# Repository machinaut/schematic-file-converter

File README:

A command line python anything-in anything-out file converter to go between the multitude of electrical circuit schematic file formats. This project was started by Alex Ray (ajray@ncsu.edu), on behalf of Upverter (http://upverter.com).

How to use:
```bash
./converter.py -i test.sch -f kicad -t json -o test.json

-i: input file
-f: from format
-t: to format
-o: output file
```

Where to Get Help:
```bash
./converter.py -h
```

Supported Formats:
  The converter started with support for KiCad. We have since been expanding it to support many of the popular open and closed source formats, as follows.
* KiCad
* Eagle (in development)
* gEDA (in development)
* Fritzing (in development)
* Altium (in development)

Format Wish List:
  This is the list of formats we wish we supported, and will work on someday (hopefully soon!). We are looking for developers to help us so please ping us if you're interested!
* DXDesigner & PADs
* Alegro
* OrCad

The Concept:
  To use an Upverter Open JSON export in another piece of software, you will need to convert it into that software's proprietary format. Likewise, to get your data out of another piece of software and import it into Upverter, you will also need to run their export through the converter. We are working to make this easier, but we will largely depend on community contribution and the participation of the other vendors.

Interchange Format Documentation:
  The converter is based on the Upverter Open JSON Format fully documented at http://upverter.com/resources/open-json-format/. We hope that someday all of the major providers of schematic capture software will support interoperability with open formats like this one.

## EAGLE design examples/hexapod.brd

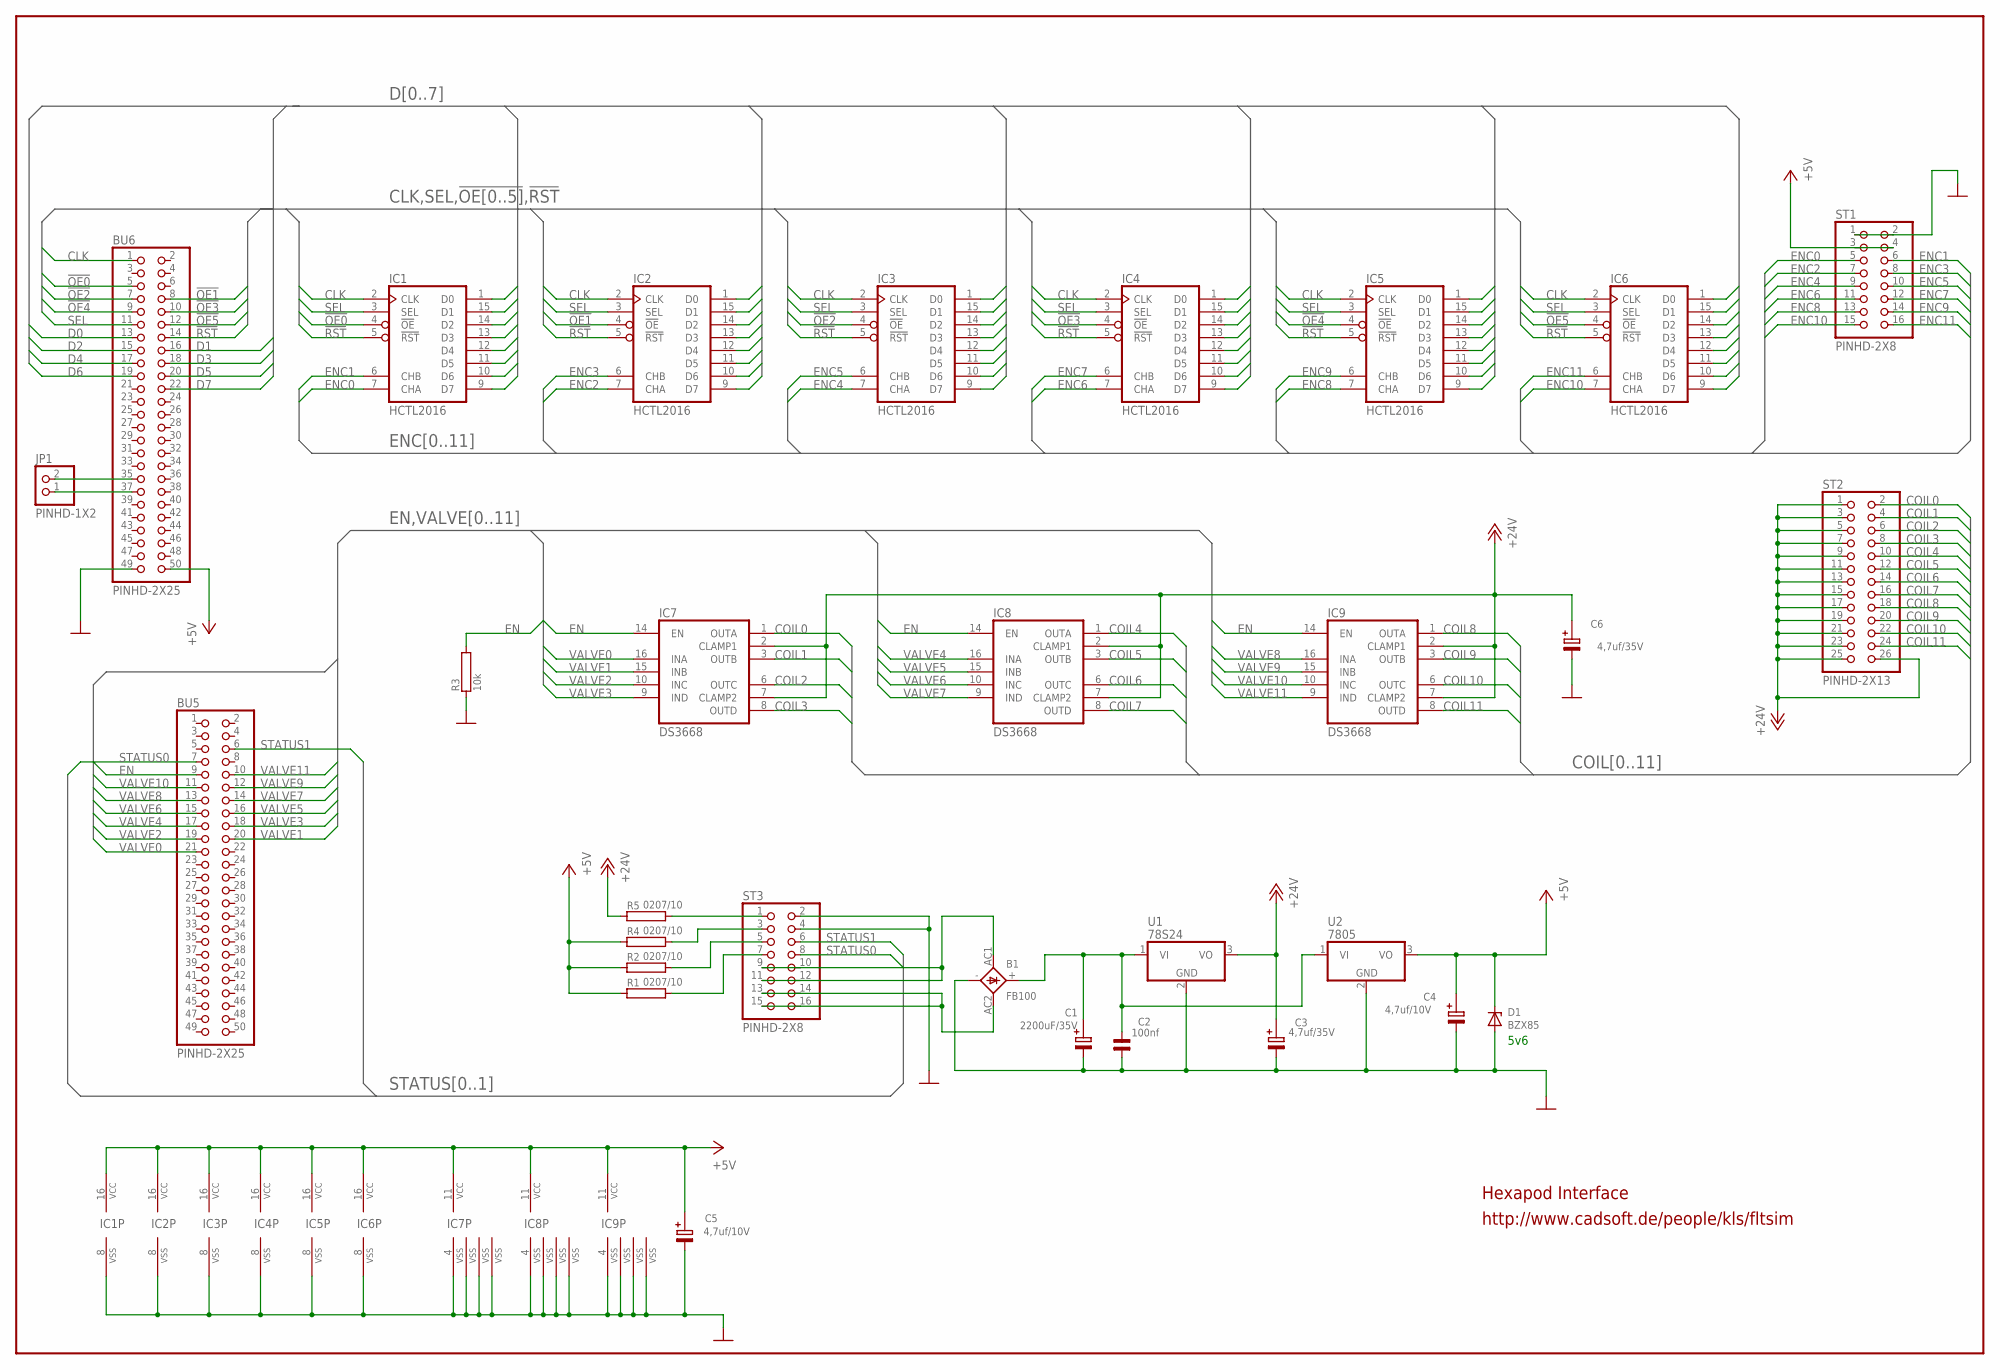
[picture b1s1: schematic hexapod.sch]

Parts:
B1: FB100
BU5, BU6: PINHD-2X25; 2X25
C1: 2200uF/35V; E35-16
C2: 100nf; C5B2,5A
C3, C6: 4,7uf/35V; E2,5-5
C4, C5: 4,7uf/10V; E2,5-5
D1: BZX85; DO41Z10
IC1, IC2, IC3, IC4, IC5, IC6: HCTL2016; DIL-16
IC7, IC8, IC9: DS3668; DIL-16
JP1: PINHD-1X2; 1X02
R1, R2, R4, R5: 0207/10
R3: 10k; 0207/10@1
ST1, ST3: PINHD-2X8; ML16
ST2: PINHD-2X13; ML26
U1: 78S24; TO220H
U2: 7805; TO220H

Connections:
!OE0: BU6.5, IC1.4 (!OE)
!OE1: BU6.8, IC2.4 (!OE)
!OE2: BU6.7, IC3.4 (!OE)
!OE3: BU6.10, IC4.4 (!OE)
!OE4: BU6.9, IC5.4 (!OE)
!OE5: BU6.12, IC6.4 (!OE)
!RST: BU6.14, IC1.5 (!RST), IC2.5 (!RST), IC3.5 (!RST), IC4.5 (!RST), IC5.5 (!RST), IC6.5 (!RST)
+5V: BU6.50, C4.+, C5.+, D1.K, IC1.16 (VCC), IC2.16 (VCC), IC3.16 (VCC), IC4.16 (VCC), IC5.16 (VCC), IC6.16 (VCC), IC7.11 (VCC), IC8.11 (VCC), IC9.11 (VCC), R1.1, R2.1, R4.1, ST1.3, ST1.4, U2.3 (VO)
+24V: C3.+, C6.+, IC7.2 (CLAMP1), IC7.7 (CLAMP2), IC8.2 (CLAMP1), IC8.7 (CLAMP2), IC9.2 (CLAMP1), IC9.7 (CLAMP2), R5.1, ST2.1, ST2.3, ST2.5, ST2.7, ST2.9, ST2.11, ST2.13, ST2.15, ST2.17, ST2.19, ST2.21, ST2.23, ST2.25, ST2.26, U1.3 (VO)
AC1: B1.AC1, ST3.9, ST3.10, ST3.11, ST3.12
AC2: B1.AC2, ST3.13, ST3.14, ST3.15, ST3.16
CLK: BU6.1, IC1.2 (CLK), IC2.2 (CLK), IC3.2 (CLK), IC4.2 (CLK), IC5.2 (CLK), IC6.2 (CLK)
COIL0: IC7.1 (OUTA), ST2.2
COIL1: IC7.3 (OUTB), ST2.4
COIL2: IC7.6 (OUTC), ST2.6
COIL3: IC7.8 (OUTD), ST2.8
COIL4: IC8.1 (OUTA), ST2.10
COIL5: IC8.3 (OUTB), ST2.12
COIL6: IC8.6 (OUTC), ST2.14
COIL7: IC8.8 (OUTD), ST2.16
COIL8: IC9.1 (OUTA), ST2.18
COIL9: IC9.3 (OUTB), ST2.20
COIL10: IC9.6 (OUTC), ST2.22
COIL11: IC9.8 (OUTD), ST2.24
D0: BU6.13, IC1.1 (D0), IC2.1 (D0), IC3.1 (D0), IC4.1 (D0), IC5.1 (D0), IC6.1 (D0)
D1: BU6.16, IC1.15 (D1), IC2.15 (D1), IC3.15 (D1), IC4.15 (D1), IC5.15 (D1), IC6.15 (D1)
D2: BU6.15, IC1.14 (D2), IC2.14 (D2), IC3.14 (D2), IC4.14 (D2), IC5.14 (D2), IC6.14 (D2)
D3: BU6.18, IC1.13 (D3), IC2.13 (D3), IC3.13 (D3), IC4.13 (D3), IC5.13 (D3), IC6.13 (D3)
D4: BU6.17, IC1.12 (D4), IC2.12 (D4), IC3.12 (D4), IC4.12 (D4), IC5.12 (D4), IC6.12 (D4)
D5: BU6.20, IC1.11 (D5), IC2.11 (D5), IC3.11 (D5), IC4.11 (D5), IC5.11 (D5), IC6.11 (D5)
D6: BU6.19, IC1.10 (D6), IC2.10 (D6), IC3.10 (D6), IC4.10 (D6), IC5.10 (D6), IC6.10 (D6)
D7: BU6.22, IC1.9 (D7), IC2.9 (D7), IC3.9 (D7), IC4.9 (D7), IC5.9 (D7), IC6.9 (D7)
EN: BU5.9, IC7.14 (EN), IC8.14 (EN), IC9.14 (EN), R3.2
ENC0: IC1.7 (CHA), ST1.5
ENC1: IC1.6 (CHB), ST1.6
ENC2: IC2.7 (CHA), ST1.7
ENC3: IC2.6 (CHB), ST1.8
ENC4: IC3.7 (CHA), ST1.9
ENC5: IC3.6 (CHB), ST1.10
ENC6: IC4.7 (CHA), ST1.11
ENC7: IC4.6 (CHB), ST1.12
ENC8: IC5.7 (CHA), ST1.13
ENC9: IC5.6 (CHB), ST1.14
ENC10: IC6.7 (CHA), ST1.15
ENC11: IC6.6 (CHB), ST1.16
GND: B1.-, BU6.49, C1.-, C2.1, C3.-, C4.-, C5.-, C6.-, D1.A, IC1.8 (VSS), IC2.8 (VSS), IC3.8 (VSS), IC4.8 (VSS), IC5.8 (VSS), IC6.8 (VSS), IC7.4 (VSS), IC7.5 (VSS), IC7.12 (VSS), IC7.13 (VSS), IC8.4 (VSS), IC8.5 (VSS), IC8.12 (VSS), IC8.13 (VSS), IC9.4 (VSS), IC9.5 (VSS), IC9.12 (VSS), IC9.13 (VSS), R3.1, ST1.1, ST1.2, ST3.2, ST3.4, U1.2 (GND), U2.2 (GND)
unnamed: R5.2, ST3.1
unnamed: R4.2, ST3.3
unnamed: R2.2, ST3.5
unnamed: R1.2, ST3.7
unnamed: BU6.35, JP1.2
unnamed: BU6.37, JP1.1
SEL: BU6.11, IC1.3 (SEL), IC2.3 (SEL), IC3.3 (SEL), IC4.3 (SEL), IC5.3 (SEL), IC6.3 (SEL)
STATUS0: BU5.7, ST3.8
STATUS1: BU5.6, ST3.6
VALVE0: BU5.21, IC7.16 (INA)
VALVE1: BU5.20, IC7.15 (INB)
VALVE2: BU5.19, IC7.10 (INC)
VALVE3: BU5.18, IC7.9 (IND)
VALVE4: BU5.17, IC8.16 (INA)
VALVE5: BU5.16, IC8.15 (INB)
VALVE6: BU5.15, IC8.10 (INC)
VALVE7: BU5.14, IC8.9 (IND)
VALVE8: BU5.13, IC9.16 (INA)
VALVE9: BU5.12, IC9.15 (INB)
VALVE10: BU5.11, IC9.10 (INC)
VALVE11: BU5.10, IC9.9 (IND)
VIN: B1.+, C1.+, C2.2, U1.1 (VI), U2.1 (VI)

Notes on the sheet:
Hexapod Interface
5v6
http://www.cadsoft.de/people/kls/fltsim

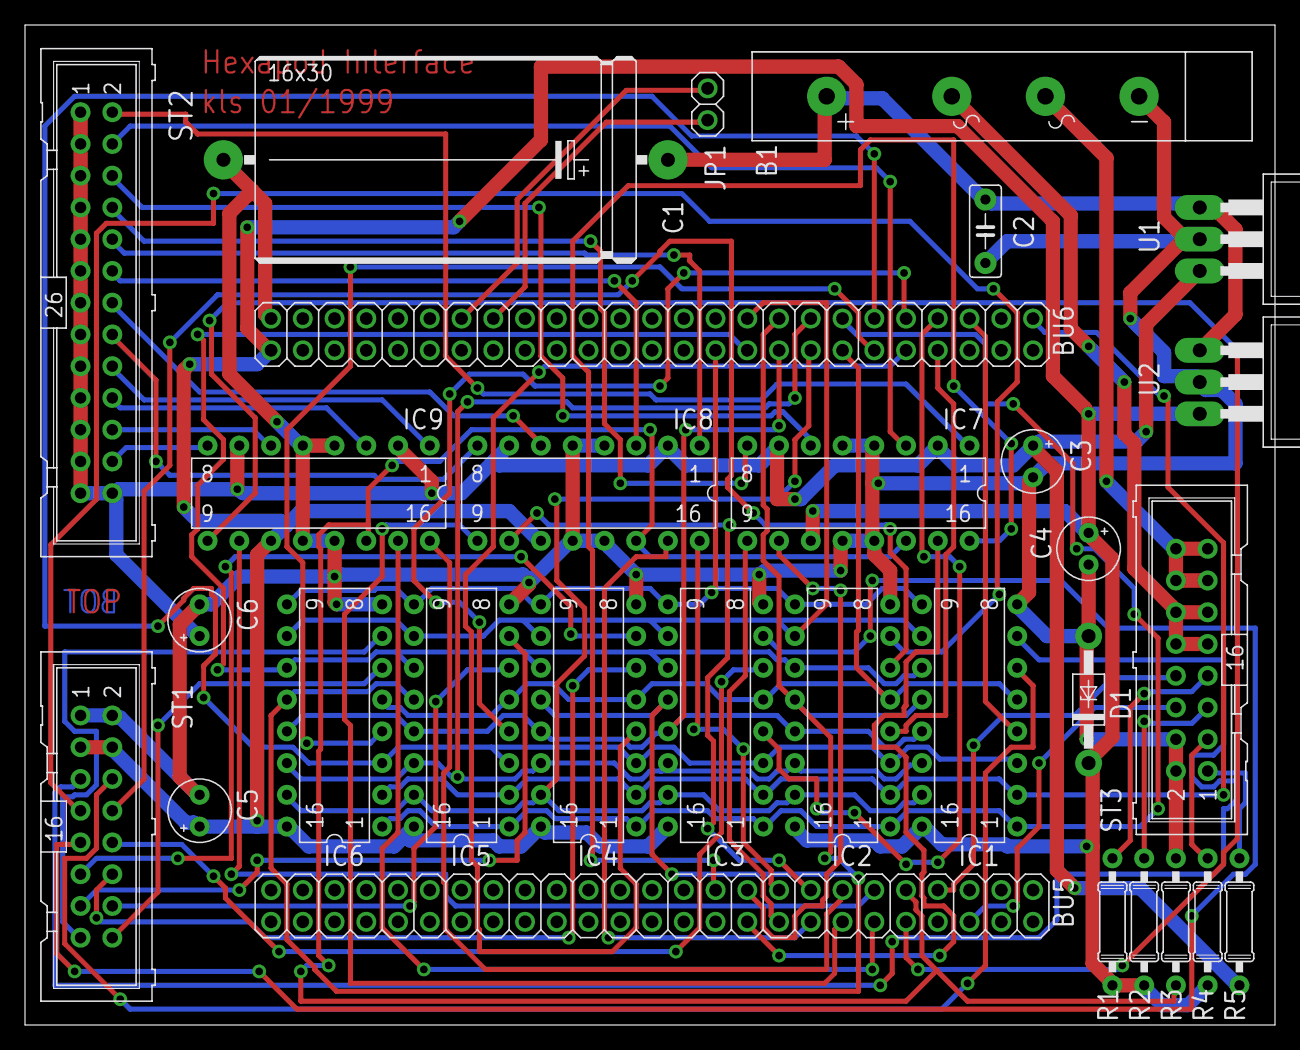
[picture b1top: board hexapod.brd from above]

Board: 2 copper layers, 100.0 x 80.0 mm, 30 parts (0 on the bottom side), 68 nets.

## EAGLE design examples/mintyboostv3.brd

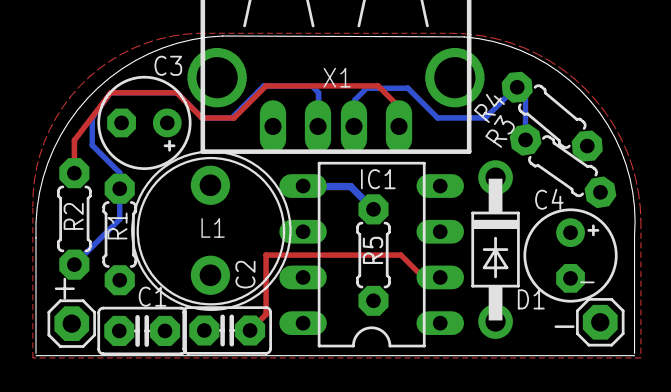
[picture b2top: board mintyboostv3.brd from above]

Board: 2 copper layers, 33.3 x 17.8 mm, 15 parts (0 on the bottom side), 8 nets.

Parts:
+: 1X01
-: 1X01
C1, C2: 0.1uF; C025-025X050
C3, C4: 220uF; E2,5-5
D1: 1N5817; DO41-7
IC1: LT1302; DIL08
L1: L; 6000
R1, R3: 49.9K; 0204/5
R2, R4: 75K; 0204/5
R5: 3.3k; 0204/5
X1: PN87520

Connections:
+5V: C4.+, D1.C, IC1.4, R2.1, R4.1, X1.1
BATT+: +.1, C1.1, C3.+, IC1.6, L1.1
D+: R1.2, R2.2, X1.3
D-: R3.2, R4.2, X1.2
GND: -.1, C1.2, C2.2, C3.-, C4.-, IC1.1, IC1.3, IC1.8, R1.1, R3.1, R5.1, X1.4
unnamed: C2.1, IC1.2
unnamed: IC1.5, R5.2
unnamed: D1.A, IC1.7, L1.2

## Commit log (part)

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2011-10-06 initial commit, beginning parsing kicad files
2011-10-06 json file format doc
2011-10-06 some classes, and trying to be smarter (dumber) about kicad format
2011-10-07 heading in for the night
2011-10-07 makin it smaller
2011-10-07 now making it more classy
2011-10-07 got segments dividing up correctly, now to clean up the debugging stuff
2011-10-07 fuck yeah, connection works
2011-10-07 woot sane net creation works
2011-10-07 removed old net calculation functions
2011-10-07 now prettyprints JSON for the nets
2011-10-07 now outputs full json, but only nets are populated
2011-10-07 rename connpoints to junctions
2011-10-08 ignore swp files
2011-10-08 remove swap files
2011-10-09 components almost there
2011-10-13 added the command to run the scritp to the README file
2011-10-13 more thinking on the format, gonna play with rendering jsonformat.json
2011-10-13 rename file
2011-10-17 nothing to see here
2011-10-19 render python script now generates basic component instances, and fully renders the example file (as it is now)
2011-10-21 removed old file format spec and added an example json file
2011-10-21 updated the example json file
2011-10-29 updating the readme file.
2011-10-29 reorg of the files.
2011-10-29 cleanup.
2011-10-29 more cleanup...
2011-10-29 polishing the documentation.
2011-10-29 last of the first pass cleanup.
2011-11-04 python script to generate an Eagle User-Level-Program that will output JSON
2011-11-04 ulp script that exporter is supposed to look like
2011-11-04 eagle type system representation in JSON. I love the meta
2011-11-04 minor todo added
2011-11-04 now ironically using an eagle representation itself in JSON
2011-11-04 Adding a file for stuff i am working on, to keep from borking the main files
2011-11-04 changing the printery things to just go to stdout for now
2011-11-04 place where one-off scripts go to die
2011-11-04 eagle barfer is tentatively done
2011-11-04 Adding template files for uvp package, which will be classes that handle uvp files
2011-11-04 Adding example upverter file json formapt
2011-11-04 json ulp changes, less whitespace
2011-11-04 typo in eagle.json, propagated
2011-11-04 Adding my orderer... I'll finish this tonight.
2011-11-05 Pushing before zzzzzz.....
2011-11-05 One useless file in up in hurrr.
2011-11-05 im about to pass out
2011-11-05 going into a programming competition, theyre going to take my laptop, see yall on the other side
2011-11-06 I made a little progress on the net class for the .uvp json format library.
2011-11-06 PREPARRE TO MERGE
2011-11-06 clean up random shit into ajray
2011-11-06 I DO ORDAIN A NEW SCHEMATIC HEIRARCHY
2011-11-06 Eagle XML format has arrived
2011-11-06 Added that the parser grabs the xml of the eagle file.
2011-11-06 Fixed previous commit
2011-11-06 Continuing to work on the xml, the xml is now in.
2011-11-06 I have a new basic strategy for eagle....
2011-11-06 multiple things
2011-11-06 make actual inclusion work and sanely print help message when run incorrectly
2011-11-06 Adding michael's schematic in the new eagle xml format, so we can nom nom nom the file into the upverter json format.
2011-11-06 eaglexml file input type
2011-11-06 eaglexml.py file, forgot last time
2011-11-06 More stuff...
2011-11-06 Getting rid of my crap.
2011-11-06 more normal-y eaglexml
2011-11-06 working on marshalling
2011-11-06 working on xml input parser
2011-11-06 makin dem shapes.
2011-11-06 Commit before fallin' asleep.
2011-11-06 rest of example file is accounted for, still does nothing on eagle xml input parsing side
2011-11-06 Cleaned up the shape.py a little bit. I need to look through the xml files, and see how shapes are defined, and create alternate constructors ( that is what the @classmethod stuff is all about) that 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
2011-11-06 gEDA/gaf File Format Document started
2011-11-06 Coordinate Space added
2011-11-06 Filenames added
2011-11-06 Object types added
2011-11-06 gEDA specific TODO file added
2011-11-06 version element added
2011-11-06 line element added
2011-11-06 layout cleanup
2011-11-06 Playing with print statements, so I understand just what we are getting from the xml. No substantial changes.
2011-11-06 picture element added
2011-11-06 Revert "Playing with print statements, so I understand just what we are getting from the xml. No substantial changes."
    This reverts commit bca2fc1c63188a0ede8de8b3fdd6b3c210425f12.
2011-11-06 box element added
2011-11-06 circle element added
2011-11-06 layout cleanup: code -> pre
2011-11-06 layout cleanup: breaks
2011-11-06 minor layout cleanups
2011-11-06 arc element added
2011-11-06 more cleaning, testing on the interpreter, seems that everything works.
2011-11-06 text element added
2011-11-06 net element added
2011-11-06 table tag closed
2011-11-06 Too much Java rots the brain.
2011-11-06 bus element added
2011-11-06 pin element added
2011-11-06 layout cleanup ... m(
2011-11-06 More progress on component.py
2011-11-06 path element added
2011-11-06 character element added
2011-11-06 Colors section added
2011-11-06 Attributes section added
2011-11-06 Embedded Components section added
2011-11-06 minor emphasis
2011-11-06 Path data section added
2011-11-06 document revision section added
2011-11-06 minor typo corrected
2011-11-06 more verbosity in eaglexml libraries
2011-11-06 Push before meetup at garage. Also, Alex, popese. That is all.
2011-11-06 more xml junk
2011-11-06 Fixed syntax
2011-11-06 More changes
2011-11-06 newpin function for shortness
2011-11-06 core/component.py is now mostly sane and has been test
2011-11-07 Added component instance beginnings
2011-11-07 instance.py
2011-11-07 more classy-ness for the core libs
2011-11-07 woot parses an instance now, just badly
2011-11-07 splitting
2011-11-07 instance parsing in eaglexml
2011-11-07 Working on eaglexml of parsing libraries, trying to get the libraries to give us something coherent for our pretty classes
2011-11-07 added the library id for library components
2011-11-07 started submitting, but still fails
2011-11-07 calling it a night, still needs to fix the component neess
2011-11-07 working on cleaning up the classes structures, in preparation for creating a recursing
2011-11-07 waaay simpler example
2011-11-07 added bogus design_attributes to put something in there
2011-11-07 removing useless shit
2011-11-07 removing test file
2011-11-07 still cleaning eaglexml.py
2011-11-07 fixed the cap example
2011-11-07 trying to fix core/design.py
2011-11-07 Forgot to add these files last time. Cleaning up core, making it more well rounded, and trying to fix stuff.
2011-11-07 cleaning up namespace, throughly checked the types of file version, component instance, design attribute, annotation, and attribute, however, i need to check the rest.
2011-11-07 parser/eaglexml.py is now got functions!
2011-11-07 prettify all of the things
2011-11-07 parser/eaglexml.py is now mostly recursive descent
2011-11-07 parser/eaglexml.py reordering parsing in order of descent
2011-11-07 fix readme usage statement
2011-11-07 add examples to readme
2011-11-07 rename json parser to openjson to let us use import json in it
2011-11-07 working on the openjson parson now
2011-11-07 parser/openjson.py open for business, minus nets
2011-11-07 parser/openjson.net appears to support nets as well. bring on the conversions
2011-11-07 bringing the eaglexml back into spec
2011-11-07 woo! think i fixed openjson parsing -> outputting
2011-11-07 header comments
2011-11-07 tiny UPV example
2011-11-07 heading to class, still trying to debug why the parser/eaglexml.py doesnt generate workable output
2011-11-07 fixed bug in way symbols were output
2011-11-07 more complex single-component example
2011-11-07 class time
2011-11-08 some new files to play with
2011-11-08 problem with curved wire - > arc parsing, but it will have to wait til after homework
2011-11-09 example from Nate Seidles latest project
2011-11-09 fixing eagle.dtd
2011-11-12 More options for initializing a Point
2011-11-14 Moved Point into shape.py and took advantage of mor flexible initialization where possible.
2011-11-14 in the middle of some nasty junk
2011-11-14 core/ added classes for all objects in OpenJSON format
2011-11-14 update README.md's example usage statement
2011-11-14 Move rename 'json' parser/writer to 'openjson'
    Having the parser/writer named 'json' caused a
    namespace conflict with python's json module.
2011-11-14 Added simple openjson test file
    test/openjson/simple.upv
2011-11-14 Modified parser/openjson.py
    - Actually parses openjson files now
    - Reads entire file as per spec into internal
    structure in core/*, and returns filled
    design object
2011-11-14 Modified writer/openjson.py
    - Connnected with changes in parser/openjson.py
2011-11-15 core.net.Net.points implemented as a dict of NetPoints, keyed on NetPoint.point_id
2011-11-15 Net.pretty_points() and Net.point_id() are no longer needed.
2011-11-15 parser.openjson updated to work with modified core.net
2011-11-15 Was using wrong function names.
2011-11-20 One change missed re: dict of NetPoints
2011-11-22 Bringing Shapes in line with upverter JSON spec.
2011-11-22 Convenience Polygon construstor
2011-11-22 Make shapes a little more general and flexible.
    - Shape.bounds() to get a square that encompasses the entire shape
    - Shape.points is a list of all the points in the shape
    - Shape.translate(dx, dy) to move the shape
    TODO:
    - Some form of Shape.rotate()
    - Maybe Shape.__getitem__ so that Shape.x == Shape.points[0].x ?
2011-11-22 Whitespace formatting
2011-11-22 bounds() works throughout the core modules.
    I don't like the amount of work that is done in core/design.Design for this, but that is the only level that has all the information it needs to work properly in scope.
2011-11-23 __getitem__ and __setitem__ for core/shape/Shape
    This way, can still use Shape.x and Shape.y, and mostly it does what it should.
2011-11-23 Taking advantage of the cahnges within the rest of core/shape
2011-11-23 Arc.bounds() is more sensible
2011-11-24 bounds() deals with 4-tuples, instead of a 2-tuple of 2-tuples
2011-11-24 Fixing some fallout from switching to 4-tuple bounds
2011-11-28 Again, missed a change re: dict of netpoints
2011-12-09 aircodeing on an airplane, lol. seriously, i probably just broke everything. ill fix it when we land
2011-12-10 incremental change, about to reorg (again, yes) to match dtd order
2011-12-10 blarg more huge changes
2011-12-10 Make the kicad parser parse the test file. Fix the test outputfile. Clean up pyflakes errors in other modules.
2011-12-11 oh god why
2011-12-11 handoff to austin
2011-12-12 Austin is pushing changes to eaglexml
2011-12-12 Austin has finished eaglexml through up to but not including basic objects in the eaglexml.dtd
2011-12-12 Finished through up to the Basic Objects line, cleaning up the use of dictionaries where elements of a list have a required name.
2011-12-12 Added Circle and Text to eaglexml stuffs.
2011-12-12 Store Points in Polygon object. Accept same inputs as Point() in addPoint().
2011-12-12 Remove backup files and ignore them.
2011-12-12 Fix bugs in openjson parser. 1. Arc angles can be floats. 2. Use correct pin points.
2011-12-12 Finished completly objectifying eagle.dtd. COMPLETELY UNTESTED CODEvim eaglexml.pyvim eaglexml.py
2011-12-13 Parse and create the component instances in a kicad file.
2011-12-13 Revert "Merge branch 'shapeup' of https://github.com/patrickyeon/schematic-file-converter into patrickyeon-shapeup"
    This reverts commit 8a426fcf6a39227bb72a4648b46ced41d07a720a, reversing
    changes made to 83c058f042dc74d175344897454196d35de70c22.
    revert the previous merge to keep the old core structure
2011-12-13 adding mins, maxs and bounding to the shapes. Based on patrickyeon-shapeup
2011-12-13 whitespace fix.
2011-12-13 adding a scons build file for lint, check and nose.
2011-12-13 lots of linter fixes.
2011-12-14 typos, added eaglexml back to upconvert.py
2011-12-15 Fix unmerged crap. whoops.
